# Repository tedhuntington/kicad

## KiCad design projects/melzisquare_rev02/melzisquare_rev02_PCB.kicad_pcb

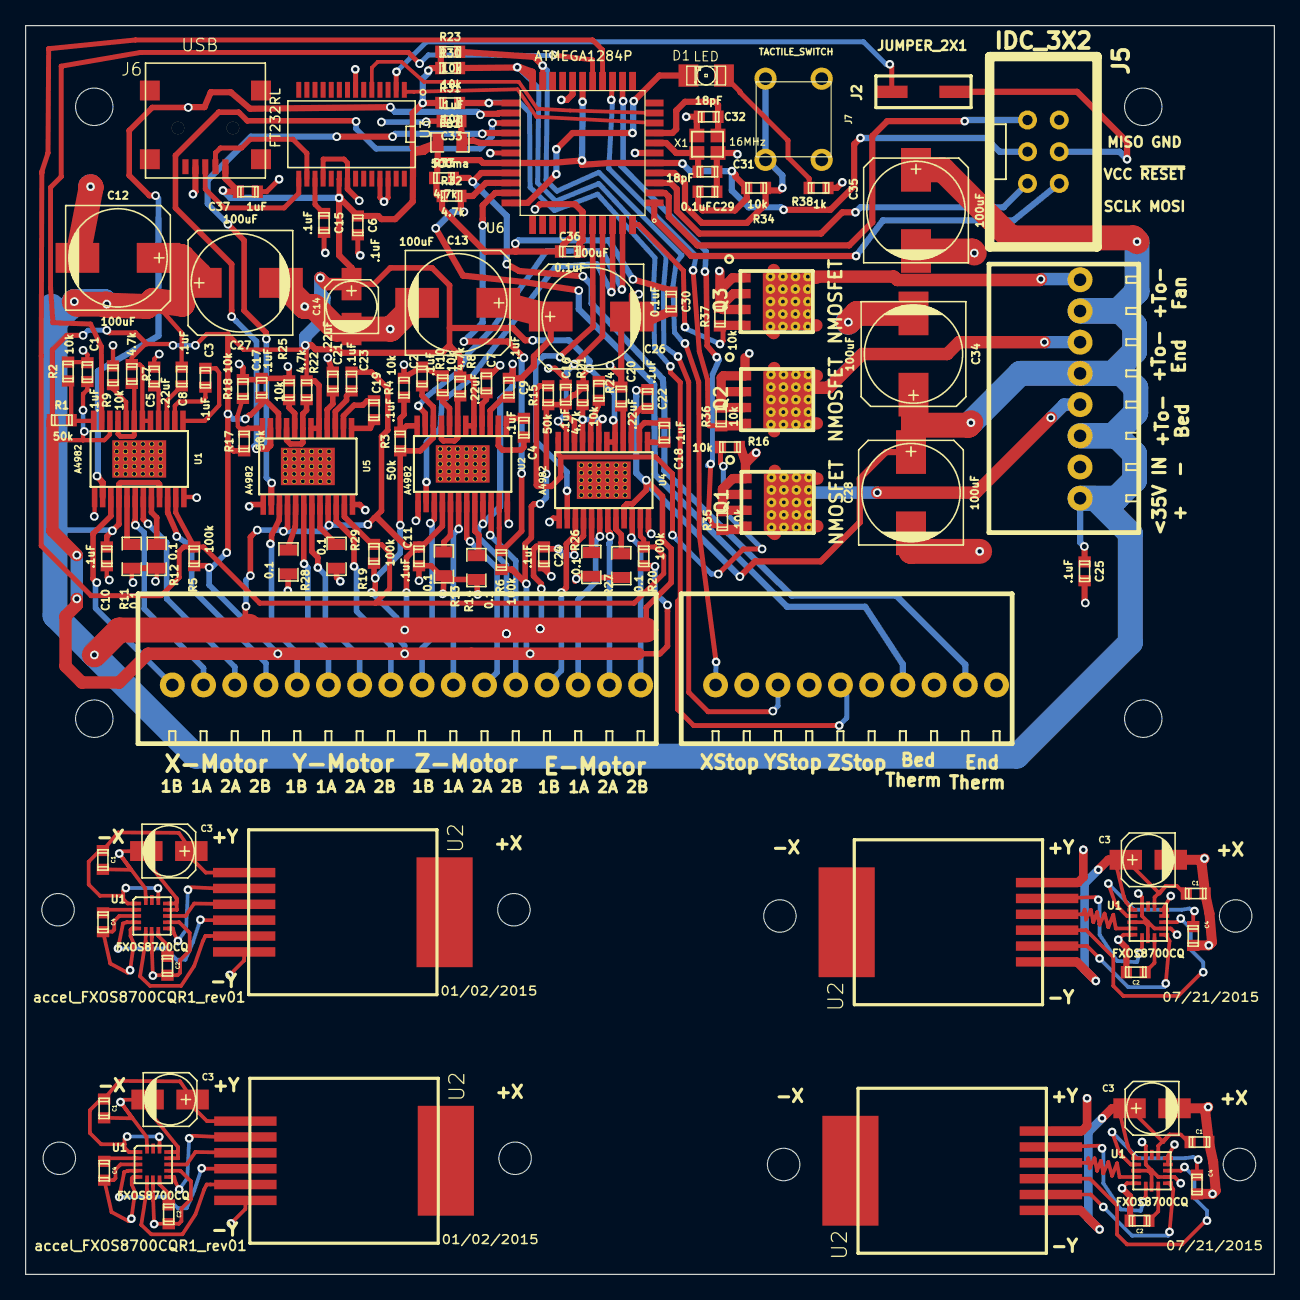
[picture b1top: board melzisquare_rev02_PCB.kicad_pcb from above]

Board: 2 copper layers, 100.0 x 100.0 mm, 130 parts (0 on the bottom side), 97 nets.

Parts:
C1, C2, C3, C4, C6, C8, C9, C10, C11, C15, C16, C17, C18, C19, C22, C23, C24, C25, C33: .1uF; TED_SM0603_C
C1#2, C1#3, C1#4, C1#5, C2#2, C2#3, C2#4, C2#5: 1uF; TED_SM0603
C3#2, C3#3, C3#4, C3#5, C14: 4.7uF; TED_c_elec_4.3x4.3
C4#2, C4#3, C4#4, C4#5: .1uF; TED_SM0603
C5, C7, C20, C21: .22uF; TED_SM0603_C
C12, C13, C26, C27, C28, C34, C35: 100uF; TED_c_elec_8mm_SMD
C29, C30, C36: 0.1uF; TED_SM0603_C
C31, C32: 18pF; TED_SM0603_C
C37: 1uF; TED_SM0603_C
D1: LED; LED-1206
FB1: 500ma; TED_SM0805_R
H1, H2, H3, H4: HOLE; TED_Hole_3mm
H1#2, H1#3, H1#4, H1#5, H2#2, H2#3, H2#4, H2#5: HOLE; TED_Hole_2_6mm
J1: TERMINAL_16X1; TED_TERMINAL_SPRING_2.54MM_16PIN_1989887
J2: JUMPER_2X1; TED_HEADER_2x1_SMT
J3: TERMINAL_10X1; TED_TERMINAL_SPRING_2.54MM_10PIN_1989829
J4: TERMINAL_8X1; TED_TERMINAL_SPRING_2.54MM_8PIN_1989803
J5: IDC_3X2; TED_IDC_3x2
J6: USB; TED_USB_SMT_MINI
J7: TACTILE_SWITCH; TED_TACTILE_SWITCH_6x6
Q1, Q2, Q3: NMOSFET; TED_SO-8_FLAT_LEAD_CASE_488AA_STYLE1
R1, R3, R15, R17: 50k; TED_SM0603_R
R2, R4, R9, R10, R16, R18, R23, R24, R25, R30, R31, R34, R35, R36, R37: 10k; TED_SM0603_R
R5, R6, R19, R20: 100k; TED_SM0603_R
R7, R8, R21, R22, R32, R33: 4.7k; TED_SM0603_R
R11, R12, R13, R14, R26, R27, R28, R29: 0.1; TED_SM0805_R
R38: 1k; TED_SM0603_R
U1, U2, U4, U5: A4982; TED_TSSOP24+PAD
U1#2, U1#3, U1#4, U1#5: FXOS8700CQ; TED_QFN16_3x5
U2#2, U2#3, U2#4, U2#5: RJ12; TED_RJ12_855135002
U3: FT232RL; TED_SSOP28
U6: ATMEGA1284P; TED_TQFP44
X1: 16MHz; TED_crystal_FA-20H

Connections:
BED-TEMP: J3.7, R32.2, U6.31
D+: J6.3, U3.15
D-: J6.2, U3.16
E-DIR: U4.14, U6.40
E-OUT1A: J1.14, U4.18
E-OUT1B: J1.13, U4.15
E-OUT2A: J1.15, U4.19
E-OUT2B: J1.16, U4.22
E-STEP: U4.11, U6.41
END-TEMP: J3.9, R33.2, U6.30
FAN: Q3.1, R37.1, U6.44
FT_RXD: U3.5, U6.10
FT_TXD: U3.1, U6.9
GND: C1.2, C1#2.2, C1#3.2, C1#4.2, C1#5.2, C2.2, C2#2.2, C2#3.2, C2#4.2, C2#5.2, C3#2.2, C3#3.2, C3#4.2, C3#5.2, C4#2.2, C4#3.2, C4#4.2, C4#5.2, C5.2, C6.2, C7.2, C10.2, C11.2, C12.2, C13.2, C14.2, C15.2, C16.2, C17.2, C20.2, C21.2, C24.2, C25.2, C26.2, C27.2, C28.2, C29.2, C30.2, C31.2, C32.2, C33.2, C34.2, C35.2, C36.2, C37.2, J3.2, J3.4, J3.6, J3.8, J3.10, J4.2, J5.6, J6.4, J7.1, J7.2, Q1.2, Q2.2, Q3.2, R2.2, R4.2, R9.2, R10.2, R11.2, R12.2, R13.2, R14.2, R16.2, R18.2, R24.2, R25.2, R26.2, R27.2, R28.2, R29.2, R35.2, R36.2, R37.2, R38.2, U1.13, U1.24, U1.PAD, U1#2.3, U1#2.5, U1#2.7, U1#2.10, U1#2.12, U1#2.13, U1#2.16, U1#3.3, U1#3.5, U1#3.7, U1#3.10, U1#3.12, U1#3.13, U1#3.16, U1#4.3, U1#4.5, U1#4.7, U1#4.10, U1#4.12, U1#4.13, U1#4.16, U1#5.3, U1#5.5, U1#5.7, U1#5.10, U1#5.12, U1#5.13, U1#5.16, U2.13, U2.24, U2.PAD, U2#2.1, U2#3.1, U2#4.1, U2#5.1, U3.7, U3.18, U3.21, U3.25, U3.26, U4.13, U4.24, U4.PAD, U5.13, U5.24, U5.PAD, U6.6, U6.18, U6.28, U6.39, X1.2, X1.4
HOTBED: Q1.1, R35.1, U6.13
HOTEND: Q2.1, R36.1, U6.14
INT1: U1#2.11, U1#3.11, U1#4.11, U1#5.11, U2#2.4, U2#3.4, U2#4.4, U2#5.4
INT2: U1#2.9, U1#3.9, U1#4.9, U1#5.9, U2#2.5, U2#3.5, U2#4.5, U2#5.5
MISO: J5.1, U6.2
MOSI: J5.4, U6.1
unnamed: C18.2, U4.2
unnamed: C4#2.1, C4#3.1, C4#4.1, C4#5.1, C18.1, U1#2.2, U1#3.2, U1#4.2, U1#5.2, U4.1
unnamed: C2#2.1, C2#3.1, C2#4.1, C2#5.1, R21.2, U1#2.8, U1#3.8, U1#4.8, U1#5.8, U4.7, U4.9
unnamed: R24.1, U4.8
unnamed: C20.1, U4.4
unnamed: C22.2, U4.3
unnamed: R26.1, U4.17
unnamed: R15.2, R16.1, U4.12
unnamed: R27.1, U4.20
unnamed: C4.2, U2.2
unnamed: C4.1, U2.1
unnamed: R8.2, U2.7, U2.9
unnamed: R10.1, U2.8
unnamed: C7.1, U2.4
unnamed: C9.2, U2.3
unnamed: R13.1, U2.17
unnamed: R14.1, U2.20
unnamed: R3.2, R4.1, U2.12
unnamed: J4.4, Q1.3
unnamed: J4.8, Q3.3
unnamed: J4.6, Q2.3
unnamed: D1.1, R38.1
unnamed: D1.2, U6.33
unnamed: C33.1, FB1.2, U6.27
unnamed: J7.3, J7.4, R34.2, U6.4
unnamed: J2.1, U3.2
unnamed: C15.1, U3.17
unnamed: C32.1, U6.8, X1.1
unnamed: C31.1, U6.7, X1.3
unnamed: R9.1, U1.8
unnamed: C5.1, U1.4
unnamed: C8.2, U1.3
unnamed: R11.1, U1.17
unnamed: C19.1, U5.1
unnamed: C19.2, U5.2
unnamed: R22.2, U5.7, U5.9
unnamed: C23.2, U5.3
unnamed: R29.1, U5.20
unnamed: R25.1, U5.8
unnamed: C21.1, U5.4
unnamed: R28.1, U5.17
unnamed: R17.2, R18.1, U5.12
unnamed: C3.1, U1.1
unnamed: C3.2, U1.2
unnamed: R7.2, U1.7, U1.9
unnamed: R12.1, U1.20
unnamed: R1.2, R2.1, U1.12
SCL: U1#2.4, U1#3.4, U1#4.4, U1#5.4, U2#2.3, U2#3.3, U2#4.3, U2#5.3
SCLK: J5.3, U6.3
SDA: U1#2.6, U1#3.6, U1#4.6, U1#5.6, U2#2.2, U2#3.2, U2#4.2, U2#5.2
VCC: C1.1, C2.1, C6.1, C14.1, C16.1, C17.1, C29.1, C30.1, C36.1, C37.1, FB1.1, J5.2, J6.1, R1.1, R3.1, R5.1, R6.1, R7.1, R8.1, R15.1, R17.1, R19.1, R20.1, R21.1, R22.1, R23.1, R30.1, R31.1, R32.1, R33.1, R34.1, U1.5, U1.6, U1.10, U2.5, U2.6, U2.10, U3.20, U4.5, U4.6, U4.10, U5.5, U5.6, U5.10, U6.5, U6.17, U6.29, U6.38
VMotor: C8.1, C9.1, C10.1, C11.1, C12.1, C13.1, C22.1, C23.1, C24.1, C25.1, C26.1, C27.1, C28.1, C34.1, C35.1, J4.1, J4.3, J4.5, J4.7, U1.16, U1.21, U2.16, U2.21, U4.16, U4.21, U5.16, U5.21
Vdd: C1#2.1, C1#3.1, C1#4.1, C1#5.1, C3#2.1, C3#3.1, C3#4.1, C3#5.1, U1#2.1, U1#2.14, U1#3.1, U1#3.14, U1#4.1, U1#4.14, U1#5.1, U1#5.14, U2#2.6, U2#3.6, U2#4.6, U2#5.6
X-DIR: U1.14, U6.24
X-OUT1A: J1.2, U1.18
X-OUT1B: J1.1, U1.15
X-OUT2A: J1.3, U1.19
X-OUT2B: J1.4, U1.22
X-STEP: U1.11, U6.16
X-STOP: J3.1, R23.2, U6.21
Y-DIR: U5.14, U6.26
Y-OUT1A: J1.6, U5.18
Y-OUT1B: J1.5, U5.15
Y-OUT2A: J1.7, U5.19
Y-OUT2B: J1.8, U5.22
Y-STEP: U5.11, U6.25
Y-STOP: J3.3, R30.2, U6.22
Z-DIR: U2.14, U6.42
Z-OUT1A: J1.10, U2.18
Z-OUT1B: J1.9, U2.15
Z-OUT2A: J1.11, U2.19
Z-OUT2B: J1.12, U2.22
Z-STEP: U2.11, U6.43
Z-STOP: J3.5, R31.2, U6.23
~RESET: J2.2, J5.5
~XYE-ENABLE: R5.2, R19.2, R20.2, U1.23, U4.23, U5.23, U6.15
~Z-ENABLE: R6.2, U2.23, U6.32

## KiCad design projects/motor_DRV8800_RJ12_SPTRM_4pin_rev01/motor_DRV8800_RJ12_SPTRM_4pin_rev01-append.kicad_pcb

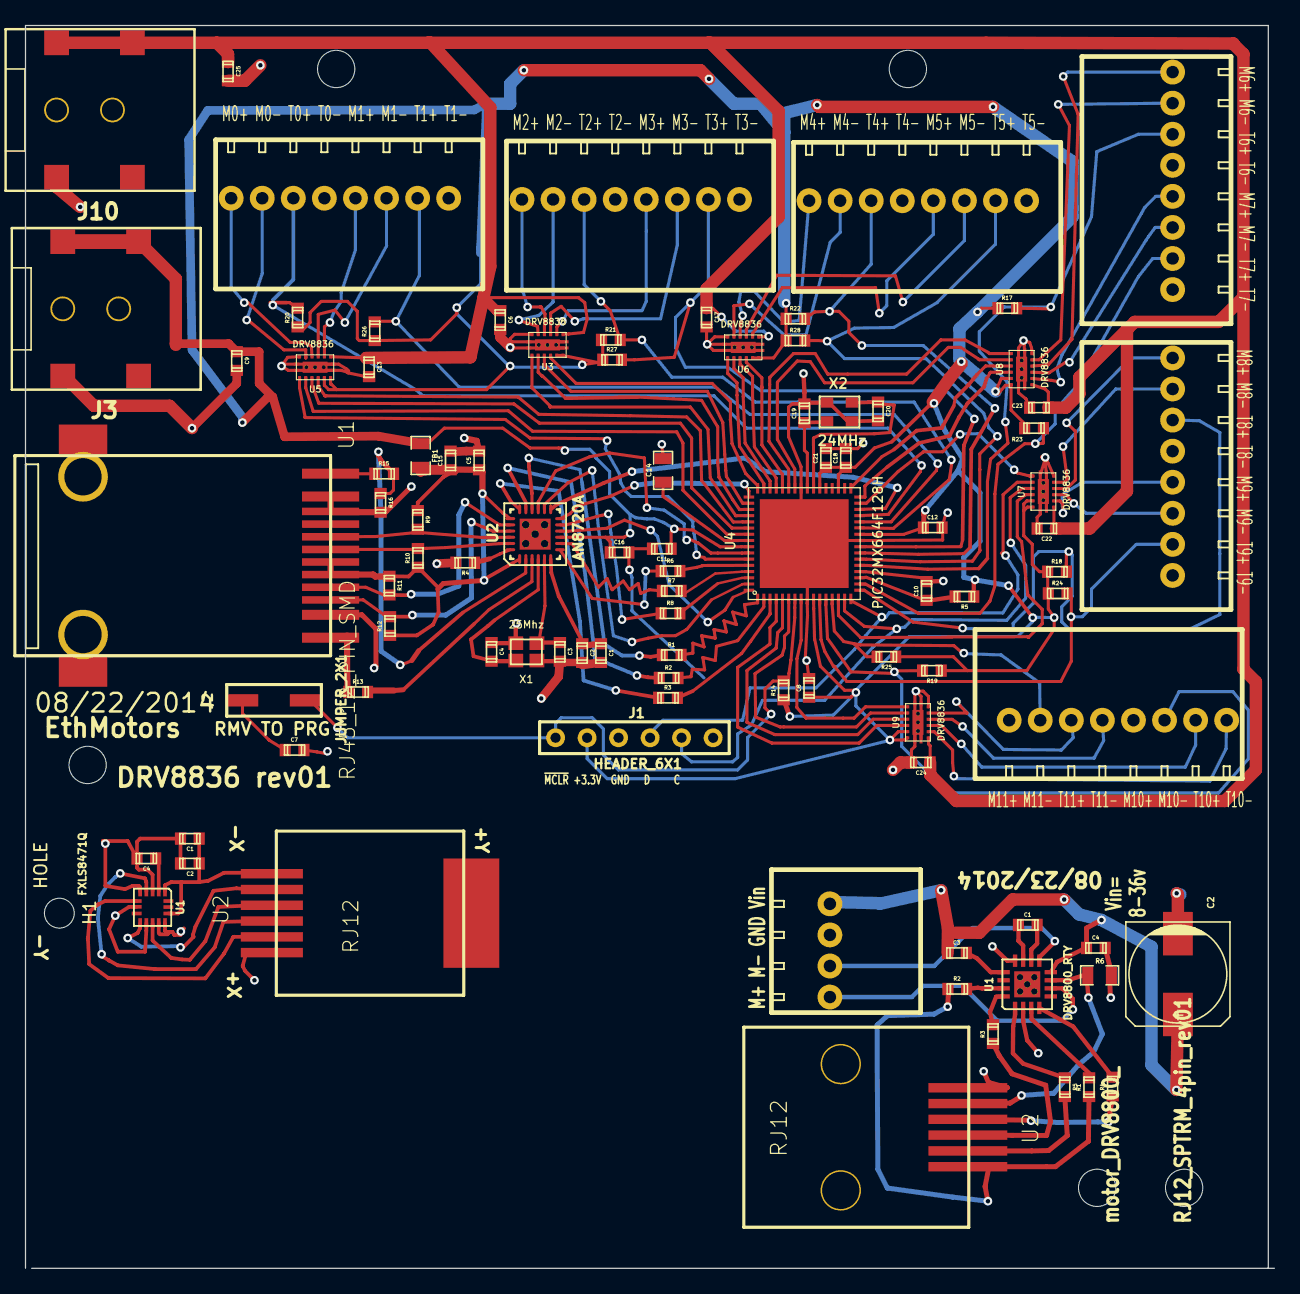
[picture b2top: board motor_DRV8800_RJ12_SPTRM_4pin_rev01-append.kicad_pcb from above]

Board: 2 copper layers, 100.5 x 100.0 mm, 99 parts (0 on the bottom side), 121 nets.

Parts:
C1, C2#2, C4#2, C5, C6, C7, C8, C10, C11, C12, C13, C16, C17, C18, C21, C22, C23, C24: .1uF; TED_SM0603
C1#2, C2, C15: 1uF; TED_SM0603
C1#3, C3#2: .1uF (50v); TED_SM0603
C2#3: 100uF 50v; TED_c_elec_8x10
C3, C4: 10pF; TED_SM0603
C4#3: .1uF 50v; TED_SM0603
C9, C25: 4.7uF; TED_SM0603
C14: 10uF (low ESR 1ohm); TED_SM0805
C19, C20: 9pF; TED_SM0603
FB1: 500mA; TED_SM0805
H1, H1#3, H2, H2#2, H4: HOLE; TED_Hole_3mm
H1#2: HOLE; TED_Hole_2_4mm
J1: HEADER_6X1; TED_HEADER_6x1
J1#2: TERMINAL_4X1; TED_TERMINAL_SPRING_2.54MM_4PIN_1989764
J2: JUMPER_2X1; TED_HEADER_2x1_SMT
J3, J10: Logic DC_2.1MM; TED_DC_2.1mm_SMT
J4, J5, J6, J7, J8, J9: TERMINAL_8X1; TED_TERMINAL_SPRING_2.54MM_8PIN_1989803
R1, R2, R3, R6, R7, R8: 33; TED_SM0603
R1#2, R2#2: 3.3k; TED_SM0603
R3#2, R4#2, R5#2, R17, R18, R19, R20, R21, R22, R23, R24, R25, R26, R27, R28: 1k; TED_SM0603
R4: 12.1k 1%; TED_SM0603
R5: 10; TED_SM0603
R6#2: 10m; TED_SM0805
R9, R10, R11, R12: 49.9; TED_SM0603
R13, R15: 249; TED_SM0603
R14: 4.7k; TED_SM0603
R16: 10k 1%; TED_SM0603
U1: RJ45_12_PIN_SMD; TED_RJ45_12pin_SMD
U1#2: FXLS8471Q; TED_QFN16_3x5
U1#3: DRV8800_RTY; TED_QFN16+1
U2: LAN8720A; TED_QFN24
U2#2: RJ12; TED_RJ12_855135002
U2#3: RJ12; TED_RJ12_955016669
U3, U5, U6, U7, U8, U9: DRV8836; TED_WSON-12
U4: PIC32MX664F128H; TED_QFN64+1
X1: 25Mhz; TED_crystal_FA-20H
X2: 24MHz; TED_crystal_TSX3225

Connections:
+3.3v: C8.1, C9.1, C11.1, C12.1, C16.1, C18.1, C21.1, FB1.1, J1.2, J3.1, R5.1, R14.1, R17.1, R18.1, R19.1, R20.1, R21.1, R22.1, R23.1, R24.1, R25.1, R26.1, R27.1, R28.1, U2.9, U3.11, U3.12, U4.10, U4.26, U4.35, U4.38, U4.57, U5.11, U5.12, U6.11, U6.12, U7.11, U7.12, U8.11, U8.12, U9.11, U9.12
AVDD: C5.1, C15.1, FB1.2, R9.1, R10.1, R11.1, R12.1, U1.5, U1.6, U2.1, U2.19
CS: R6#2.1, U1#3.7, U2#3.2
ECRSDV: R8.2, U4.62
EMDC: U2.13, U4.30
EMDIO: U2.12, U4.49
EREFCLK: U2.14, U4.63
ERXD0: R7.2, U4.61
ERXD1: R6.2, U4.60
ERXERR: U2.10, U4.64
ETXD0: R2.2, U4.2
ETXD1: R3.2, U4.3
ETXEN: R1.2, U4.1
GND: C1.2, C1#2.2, C2.2, C2#2.2, C2#3.2, C3.2, C4.1, C4#2.2, C4#3.2, C5.2, C6.2, C7.2, C8.2, C9.2, C10.2, C11.2, C12.2, C13.2, C14.2, C15.2, C16.2, C17.2, C18.2, C19.2, C20.2, C21.2, C22.2, C23.2, C24.2, C25.2, J1.3, J1#2.2, J3.2, J4.1, J4.5, J5.1, J5.5, J6.1, J6.5, J7.1, J7.5, J8.1, J8.5, J9.1, J9.5, J10.2, R4.2, R6#2.2, R16.2, U1.2, U1.10, U1.11, U1#2.3, U1#2.5, U1#2.7, U1#2.10, U1#2.12, U1#2.13, U1#3.2, U1#3.12, U1#3.17, U2.25, U2#2.1, U2#3.1, U3.6, U3.PP, U4.9, U4.20, U4.25, U4.41, U4.65, U5.6, U5.PP, U6.6, U6.PP, U7.6, U7.PP, U8.6, U8.PP, U9.6, U9.PP, X1.2, X1.4, X2.2, X2.4
GreenLED: R15.1, U1.12
INT1: U1#2.11, U2#2.4
INT2: U1#2.9, U2#2.5
M0+: J7.8, U5.4
M0-: J7.7, U5.5
M1+: J7.4, U5.2
M1-: J7.3, U5.3
M2+: J8.8, U3.4
M2-: J8.7, U3.5
M3+: J8.4, U3.2
M3-: J8.3, U3.3
M4+: J9.8, U6.4
M4-: J9.7, U6.5
M5+: J9.4, U6.2
M5-: J9.3, U6.3
M6+: J4.8, U8.4
M6-: J4.7, U8.5
M7+: J4.4, U8.2
M7-: J4.3, U8.3
M8+: J5.8, U7.4
M8-: J5.7, U7.5
M9+: J5.4, U7.2
M9-: J5.3, U7.3
M10+: J6.8, U9.2
M10-: J6.7, U9.3
M11+: J6.4, U9.4
M11-: J6.3, U9.5
MODE: R3#2.2, U1#3.16
Motor1OutA: J1#2.4, U1#3.6
Motor1OutB: J1#2.3, U1#3.9
unnamed: C1#3.1, U1#3.11
unnamed: C1#3.2, U1#3.10
unnamed: R2#2.2, U1#3.15
unnamed: R1#2.2, U1#3.3
unnamed: C4#2.1, U1#2.2
unnamed: R5#2.2, U2#3.5
unnamed: R4#2.1, U2#3.3
unnamed: R3#2.1, U2#3.4
unnamed: C3#2.2, U1#3.13
unnamed: R8.1, U2.11
unnamed: R3.1, U2.18
unnamed: R2.1, U2.17
unnamed: R1.1, U2.16
unnamed: R13.2, U2.3
unnamed: R15.2, R16.1, U2.2
unnamed: R4.1, U2.24
unnamed: R7.1, U2.8
unnamed: R6.1, U2.7
unnamed: C1.1, C2.1, U2.6
unnamed: C7.1, J2.1
unnamed: C4.2, U2.4, X1.3
unnamed: C3.1, U2.5, X1.1
unnamed: C10.1, R5.2, U4.19
unnamed: C19.1, U4.40, X2.1
unnamed: C20.1, U4.39, X2.3
PGEC1_RB1: J1.5, U4.15, U7.9
PGED1_RB0: J1.4, U4.16, U7.8
PHASE: R5#2.1, U1#3.1
PWM: R4#2.2, U1#3.4
RB2: U4.14, U7.10
RB3: J6.2, R25.2, U4.13
RB4: J6.6, R19.2, U4.12
RB5: J5.2, R24.2, U4.11
RB6: J5.6, R18.2, U4.17
RB7: J4.2, R23.2, U4.18
RB8: J4.6, R17.2, U4.21
RB9: J9.2, R28.2, U4.22
RB10: J9.6, R22.2, U4.23
RB11: J8.2, R27.2, U4.24
RB12: J8.6, R21.2, U4.27
RB13: J7.2, R26.2, U4.28
RB14: J7.6, R20.2, U4.29
RC13: U4.47, U6.7
RC14: U3.10, U4.48
RD0: U4.46, U6.8
RD2: U3.9, U4.50
RD3: U3.8, U4.51
RD4: U3.7, U4.52
RD5: U4.53, U5.10
RD6: U4.54, U5.9
RD7: U4.55, U5.8
RD8: U4.42, U8.8
RD9: U4.43, U8.7
RD10: U4.44, U6.10
RD11: U4.45, U6.9
RF1: U4.59, U5.7
RF3: U4.33, U8.9
RF4: U4.31, U7.7
RF5: U4.32, U8.10
RG6: U4.4, U9.10
RG7: U4.5, U9.9
RG8: U4.6, U9.8
RG9: U4.8, U9.7
RXN: R9.2, U1.8, U2.22
RXP: R10.2, U1.7, U2.23
SCL: U1#2.4, U2#2.3
SDA: U1#2.6, U2#2.2
TXN: R11.2, U1.4, U2.20
TXP: R12.2, U1.3, U2.21
VCAP: C14.1, U4.56
VDD: R1#2.1, R2#2.1, U2#3.6
VMotor: C6.1, C13.1, C17.1, C22.1, C23.1, C24.1, C25.1, J10.1, U3.1, U5.1, U6.1, U7.1, U8.1, U9.1
Vdd: C1#2.1, C2#2.1, U1#2.1, U1#2.14, U2#2.6
Vin: C2#3.1, C3#2.1, C4#3.1, J1#2.1, U1#3.8
YellowLED: R13.1, U1.1
nRST: U2.15, U4.58
~MCLR~: J1.1, J2.2, R14.2, U4.7

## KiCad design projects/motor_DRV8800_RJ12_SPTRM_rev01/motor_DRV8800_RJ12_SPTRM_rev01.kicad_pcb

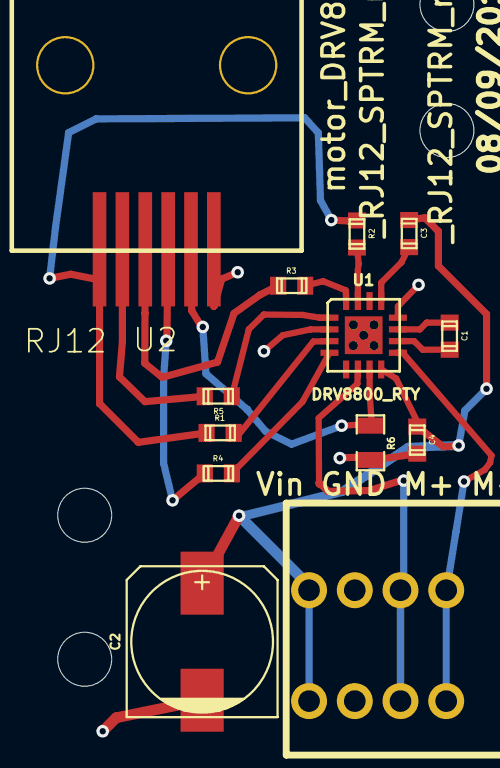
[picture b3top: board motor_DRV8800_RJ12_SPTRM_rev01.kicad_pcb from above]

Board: 2 copper layers, 17 parts (0 on the bottom side), 17 nets.

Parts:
C1, C3: .1uF (50v); TED_SM0603
C2: 100uF 50v; TED_c_elec_8x10
C4: .1uF 50v; TED_SM0603
H1, H2, H3, H4: HOLE; TED_Hole_3mm
J1: TERMINAL_4X1; TED_TERMINAL_SPRING_2.54MM_4PIN
R1, R2: 3.3k; TED_SM0603
R3, R4, R5: 1k; TED_SM0603
R6: 10m; TED_SM0805
U1: DRV8800_RTY; TED_QFN16+1
U2: RJ12; TED_RJ12_955016669

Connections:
CS: R6.1, U1.7, U2.2
GND: C2.2, C4.2, J1.2, R6.2, U1.2, U1.12, U1.17, U2.1
MODE: R3.2, U1.16
Motor1OutA: J1.3, U1.6
Motor1OutB: J1.4, U1.9
unnamed: C1.1, U1.11
unnamed: C1.2, U1.10
unnamed: R1.2, U1.3
unnamed: R4.1, U2.3
unnamed: R3.1, U2.4
unnamed: R5.2, U2.5
unnamed: C3.2, U1.13
unnamed: R2.2, U1.15
PHASE: R5.1, U1.1
PWM: R4.2, U1.4
VDD: R1.1, R2.1, U2.6
Vin: C2.1, C3.1, C4.1, J1.1, U1.8

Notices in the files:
projects/melzisquare_rev02/melzisquare_rev02_PCB.kicad_pcb:
melzisquare_rev02  License: GPL  09/02/2015
